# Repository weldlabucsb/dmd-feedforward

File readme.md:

# Digital Micromirror Device (DMD) Control and Optimization

Provides display control and feedback for the DLP9000 / LC9000 EVM DMD package using a Femto Easy beam profiler (LP6.3).

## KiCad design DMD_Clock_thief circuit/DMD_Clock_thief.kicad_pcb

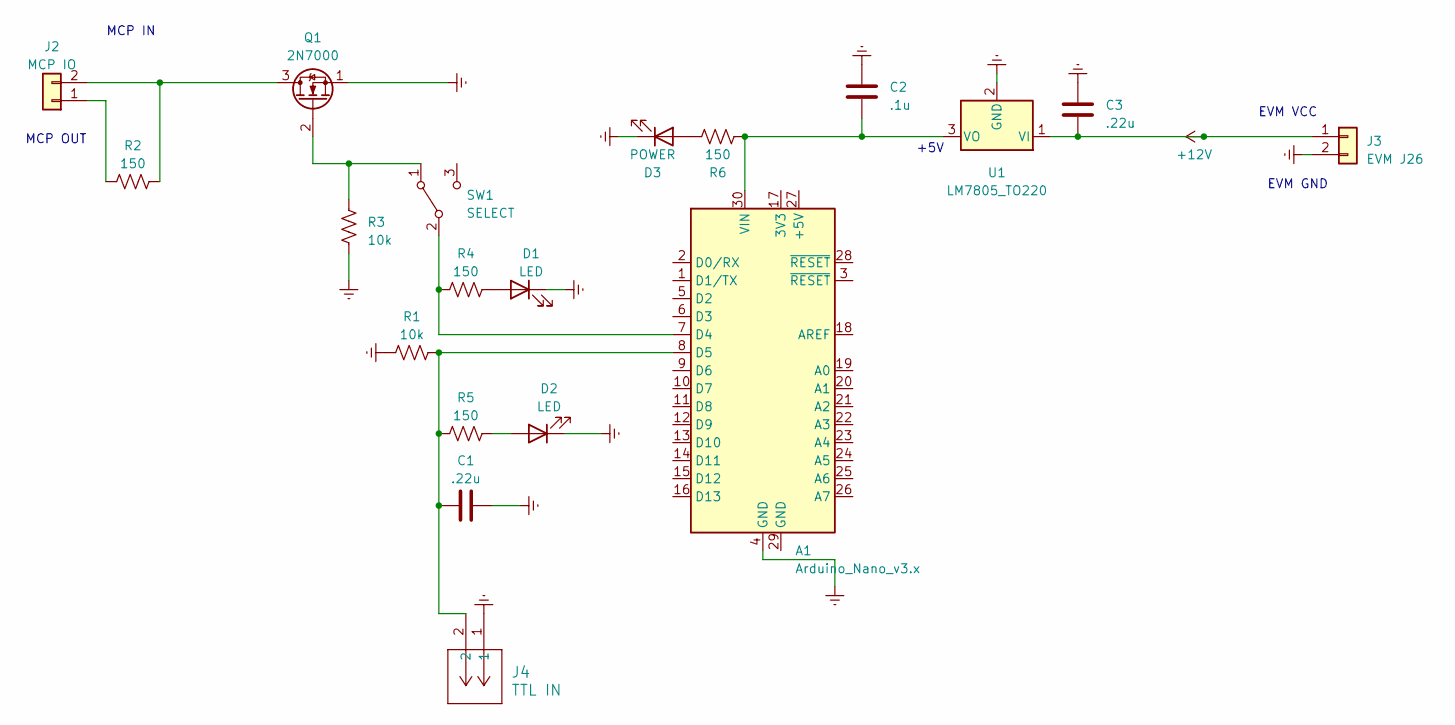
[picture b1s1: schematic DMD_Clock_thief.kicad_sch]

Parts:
A1: Arduino_Nano_v3.x; Arduino_Nano
C1, C3: .22u; C_Disc_D9.0mm_W2.5mm_P5.00mm
C2: .1u; C_Disc_D9.0mm_W2.5mm_P5.00mm
D1, D2: LED; LED_D5.0mm
D3: POWER; LED_D5.0mm
J2: MCP IO; PinHeader_1x02_P2.54mm_Vertical
J3: EVM J26; PinHeader_1x02_P2.54mm_Vertical
J4: TTL IN; CONN_CONBN_LNX
Q1: 2N7000; TO-92_Inline
R1, R3: 10k; R_Axial_DIN0207_L6.3mm_D2.5mm_P10.16mm_Horizontal
R2, R4, R5, R6: 150; R_Axial_DIN0207_L6.3mm_D2.5mm_P10.16mm_Horizontal
SW1: SELECT; PinHeader_1x03_P2.54mm_Vertical
U1: LM7805_TO220; TO-220-3_Vertical

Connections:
+12V: C3.2, J3.1, U1.1 (VI)
Earth: A1.4 (GND), C1.2, C2.1, C3.1, D1.1 (K), D2.1 (K), D3.1 (K), J3.2, J4.1, Q1.1 (S), R1.1, R3.2, U1.2 (GND)
unnamed: A1.7 (D4), R4.1, SW1.2 (B)
unnamed: A1.8 (D5), C1.1, J4.2, R1.2, R5.1
unnamed: A1.30 (VIN), C2.2, R6.1, U1.3 (VO)
unnamed: D1.2 (A), R4.2
unnamed: D2.2 (A), R5.2
unnamed: D3.2 (A), R6.2
unnamed: J2.1, R2.1
unnamed: J2.2, Q1.3 (D), R2.2
unnamed: Q1.2 (G), R3.1, SW1.1 (A)

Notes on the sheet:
+5V
EVM GND
MCP OUT
EVM VCC
MCP IN

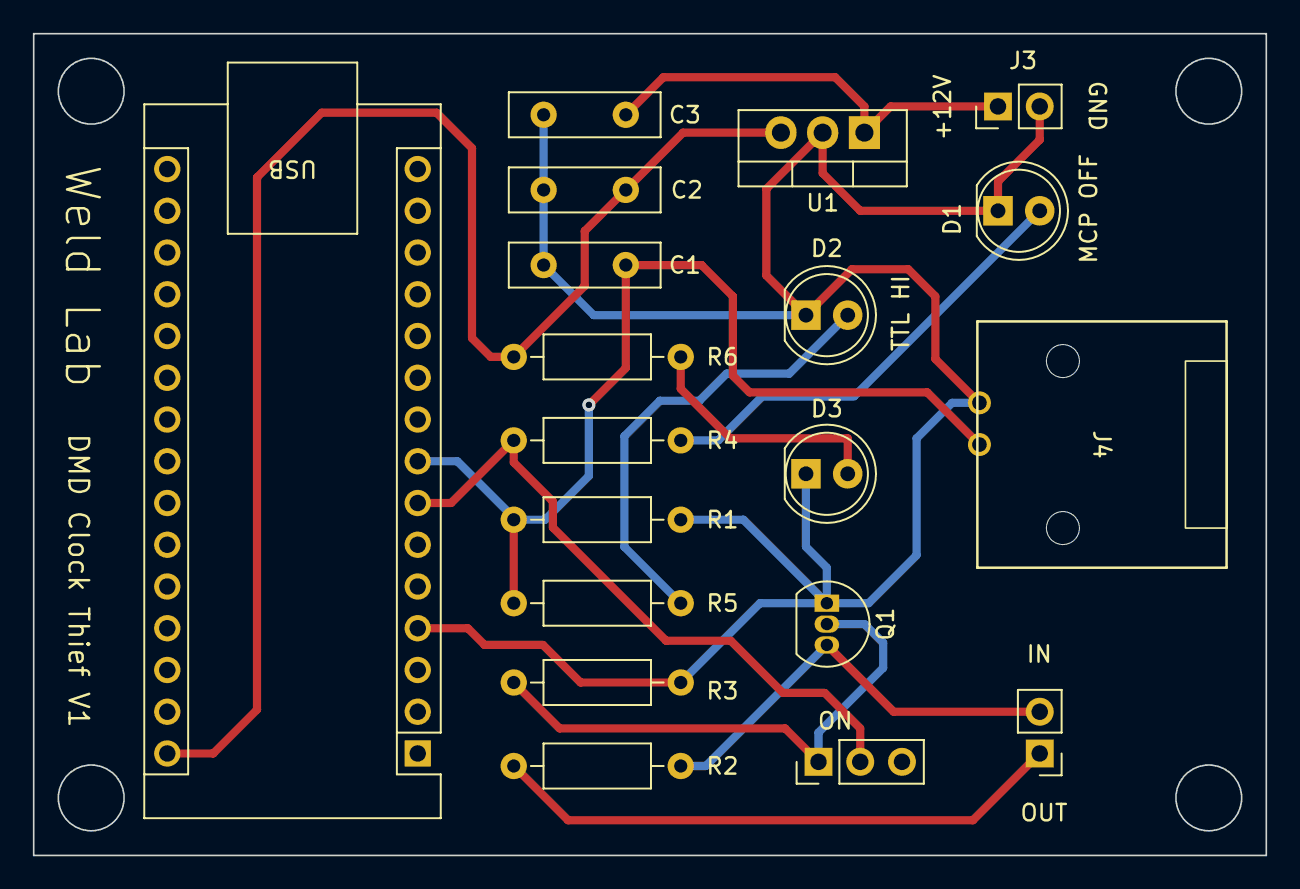
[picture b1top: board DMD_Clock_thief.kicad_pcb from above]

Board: 2 copper layers, 75.0 x 50.0 mm, 19 parts (0 on the bottom side), 11 nets.

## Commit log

2024-08-21 intial commit
2024-08-21 Update DMDController.py
    added header doc
2024-08-21 Update Feedforward.py
    fixed computed flat to divide by fit instead of subtract
2024-08-21 updated docs
2024-08-21 cleaned up
2024-08-22 file headers
2024-08-23 fixed plotting
2024-08-23 updated pins to match pcb
